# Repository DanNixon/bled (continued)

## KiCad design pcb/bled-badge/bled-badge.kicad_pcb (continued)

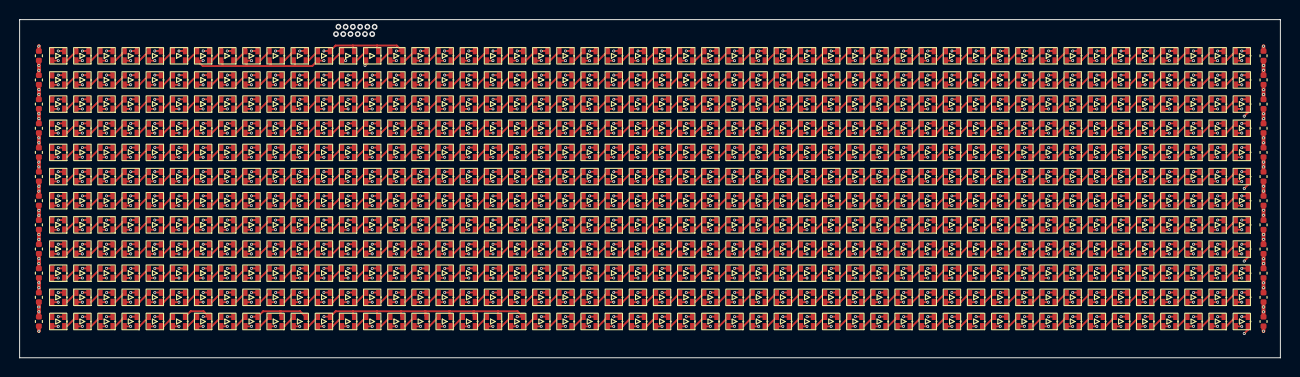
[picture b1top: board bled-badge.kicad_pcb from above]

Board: 4 copper layers, 130.5 x 35.0 mm, 625 parts (1 on the bottom side), 602 nets.

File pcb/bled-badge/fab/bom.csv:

Comment,Designator,Footprint,LCSC
10u,"C1,C2,C3,C4,C5,C6,C7,C8,C9,C10,C11,C12,C13,C14,C15,C16,C17,C18,C19,C20,C21,C22,C23,C24",Capacitor_SMD:C_0402_1005Metric,C15525
,U1,bled:BLED_Stamp,
XL-1615RGBC-WS2812B-S,"D1,D2,D3,D4,D5,D6,D7,D8,D9,D10,D11,D12,D13,D14,D15,D16,D17,D18,D19,D20,D21,D22,D23,D24,D25,D26,D27,D28,D29,D30,D31,D32,D33,D34,D35,D36,D37,D38,D39,D40,D41,D42,D43,D44,D45,D46,D47,D48,D49,D50,D51,D52,D53,D54,D55,D56,D57,D58,D59,D60,D61,D62,D63,D64,D65,D66,D67,D68,D69,D70,D71,D72,D73,D74,D75,D76,D77,D78,D79,D80,D81,D82,D83,D84,D85,D86,D87,D88,D89,D90,D91,D92,D93,D94,D95,D96,D97,D98,D99,D100",bled:XL-1615RGBC-2812B-S,C41413180
XL-1615RGBC-WS2812B-S,"D101,D102,D103,D104,D105,D106,D107,D108,D109,D110,D111,D112,D113,D114,D115,D116,D117,D118,D119,D120,D121,D122,D123,D124,D125,D126,D127,D128,D129,D130,D131,D132,D133,D134,D135,D136,D137,D138,D139,D140,D141,D142,D143,D144,D145,D146,D147,D148,D149,D150,D151,D152,D153,D154,D155,D156,D157,D158,D159,D160,D161,D162,D163,D164,D165,D166,D167,D168,D169,D170,D171,D172,D173,D174,D175,D176,D177,D178,D179,D180,D181,D182,D183,D184,D185,D186,D187,D188,D189,D190,D191,D192,D193,D194,D195,D196,D197,D198,D199,D200",bled:XL-1615RGBC-2812B-S,C41413180
XL-1615RGBC-WS2812B-S,"D201,D202,D203,D204,D205,D206,D207,D208,D209,D210,D211,D212,D213,D214,D215,D216,D217,D218,D219,D220,D221,D222,D223,D224,D225,D226,D227,D228,D229,D230,D231,D232,D233,D234,D235,D236,D237,D238,D239,D240,D241,D242,D243,D244,D245,D246,D247,D248,D249,D250,D251,D252,D253,D254,D255,D256,D257,D258,D259,D260,D261,D262,D263,D264,D265,D266,D267,D268,D269,D270,D271,D272,D273,D274,D275,D276,D277,D278,D279,D280,D281,D282,D283,D284,D285,D286,D287,D288,D289,D290,D291,D292,D293,D294,D295,D296,D297,D298,D299,D300",bled:XL-1615RGBC-2812B-S,C41413180
XL-1615RGBC-WS2812B-S,"D301,D302,D303,D304,D305,D306,D307,D308,D309,D310,D311,D312,D313,D314,D315,D316,D317,D318,D319,D320,D321,D322,D323,D324,D325,D326,D327,D328,D329,D330,D331,D332,D333,D334,D335,D336,D337,D338,D339,D340,D341,D342,D343,D344,D345,D346,D347,D348,D349,D350,D351,D352,D353,D354,D355,D356,D357,D358,D359,D360,D361,D362,D363,D364,D365,D366,D367,D368,D369,D370,D371,D372,D373,D374,D375,D376,D377,D378,D379,D380,D381,D382,D383,D384,D385,D386,D387,D388,D389,D390,D391,D392,D393,D394,D395,D396,D397,D398,D399,D400",bled:XL-1615RGBC-2812B-S,C41413180
XL-1615RGBC-WS2812B-S,"D401,D402,D403,D404,D405,D406,D407,D408,D409,D410,D411,D412,D413,D414,D415,D416,D417,D418,D419,D420,D421,D422,D423,D424,D425,D426,D427,D428,D429,D430,D431,D432,D433,D434,D435,D436,D437,D438,D439,D440,D441,D442,D443,D444,D445,D446,D447,D448,D449,D450,D451,D452,D453,D454,D455,D456,D457,D458,D459,D460,D461,D462,D463,D464,D465,D466,D467,D468,D469,D470,D471,D472,D473,D474,D475,D476,D477,D478,D479,D480,D481,D482,D483,D484,D485,D486,D487,D488,D489,D490,D491,D492,D493,D494,D495,D496,D497,D498,D499,D500",bled:XL-1615RGBC-2812B-S,C41413180
XL-1615RGBC-WS2812B-S,"D501,D502,D503,D504,D505,D506,D507,D508,D509,D510,D511,D512,D513,D514,D515,D516,D517,D518,D519,D520,D521,D522,D523,D524,D525,D526,D527,D528,D529,D530,D531,D532,D533,D534,D535,D536,D537,D538,D539,D540,D541,D542,D543,D544,D545,D546,D547,D548,D549,D550,D551,D552,D553,D554,D555,D556,D557,D558,D559,D560,D561,D562,D563,D564,D565,D566,D567,D568,D569,D570,D571,D572,D573,D574,D575,D576,D577,D578,D579,D580,D581,D582,D583,D584,D585,D586,D587,D588,D589,D590,D591,D592,D593,D594,D595,D596,D597,D598,D599,D600",bled:XL-1615RGBC-2812B-S,C41413180

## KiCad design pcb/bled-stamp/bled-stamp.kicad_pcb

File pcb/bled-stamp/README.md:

# BLED stamp

A small stamp-like PCB that can be designed onto lights, etc.
Mostly equivalent to the [backpack PCB](../bled-pico-w-backpack), but with a BMS and in a form factor easier to mount onto a larger PCB.

Features:

- All of the features of the backpack PCB
- Single cell lipo battery charging/management
- Some extra IO on the castellations
- USB C (with debug on sideband pins)

## Power

There are three main options for powering an installation with the stamp:

### 1) USB only

- Do not connect a lipo battery
- Do not connect a 5V supply to "5V IN"
- Power LEDs from "5V OUT"

### 2) battery

- Connect a single cell lipo battery to either the onboard connector or "BATT+", not both
- Do not connect a 5V supply to "5V IN"
- Power LEDs from "5V OUT"

When USB is also connected, LEDs will be powered from VBUS and battery will be recharged.

It is possible to turn off the LED power whilst leaving the MCU powered for low power standby.

### 3) external

- Do not connect a lipo battery
- Connect a 5V supply to "5V IN"
- Power LEDs from the external supply, not "5V OUT"

When USB is connected, logic will be powered from the higher of VBUS or "5V IN".

## Testing

Hardware testing checklist:

- Power from USB A-C cable in both orientations
- Power from USB C-C cable in both orientations
- Flashing firmware via SWD on type C sideband pins
- USB data
- User buttons
- SD card slot
- LED outputs
- Boot MCU into bootloader mode
- BMS
  - Interface with MCU
  - Power from battery
  - Battery charging
  - Boost converter working (5V LED power)
- BLE interface (if RM2 fitted)

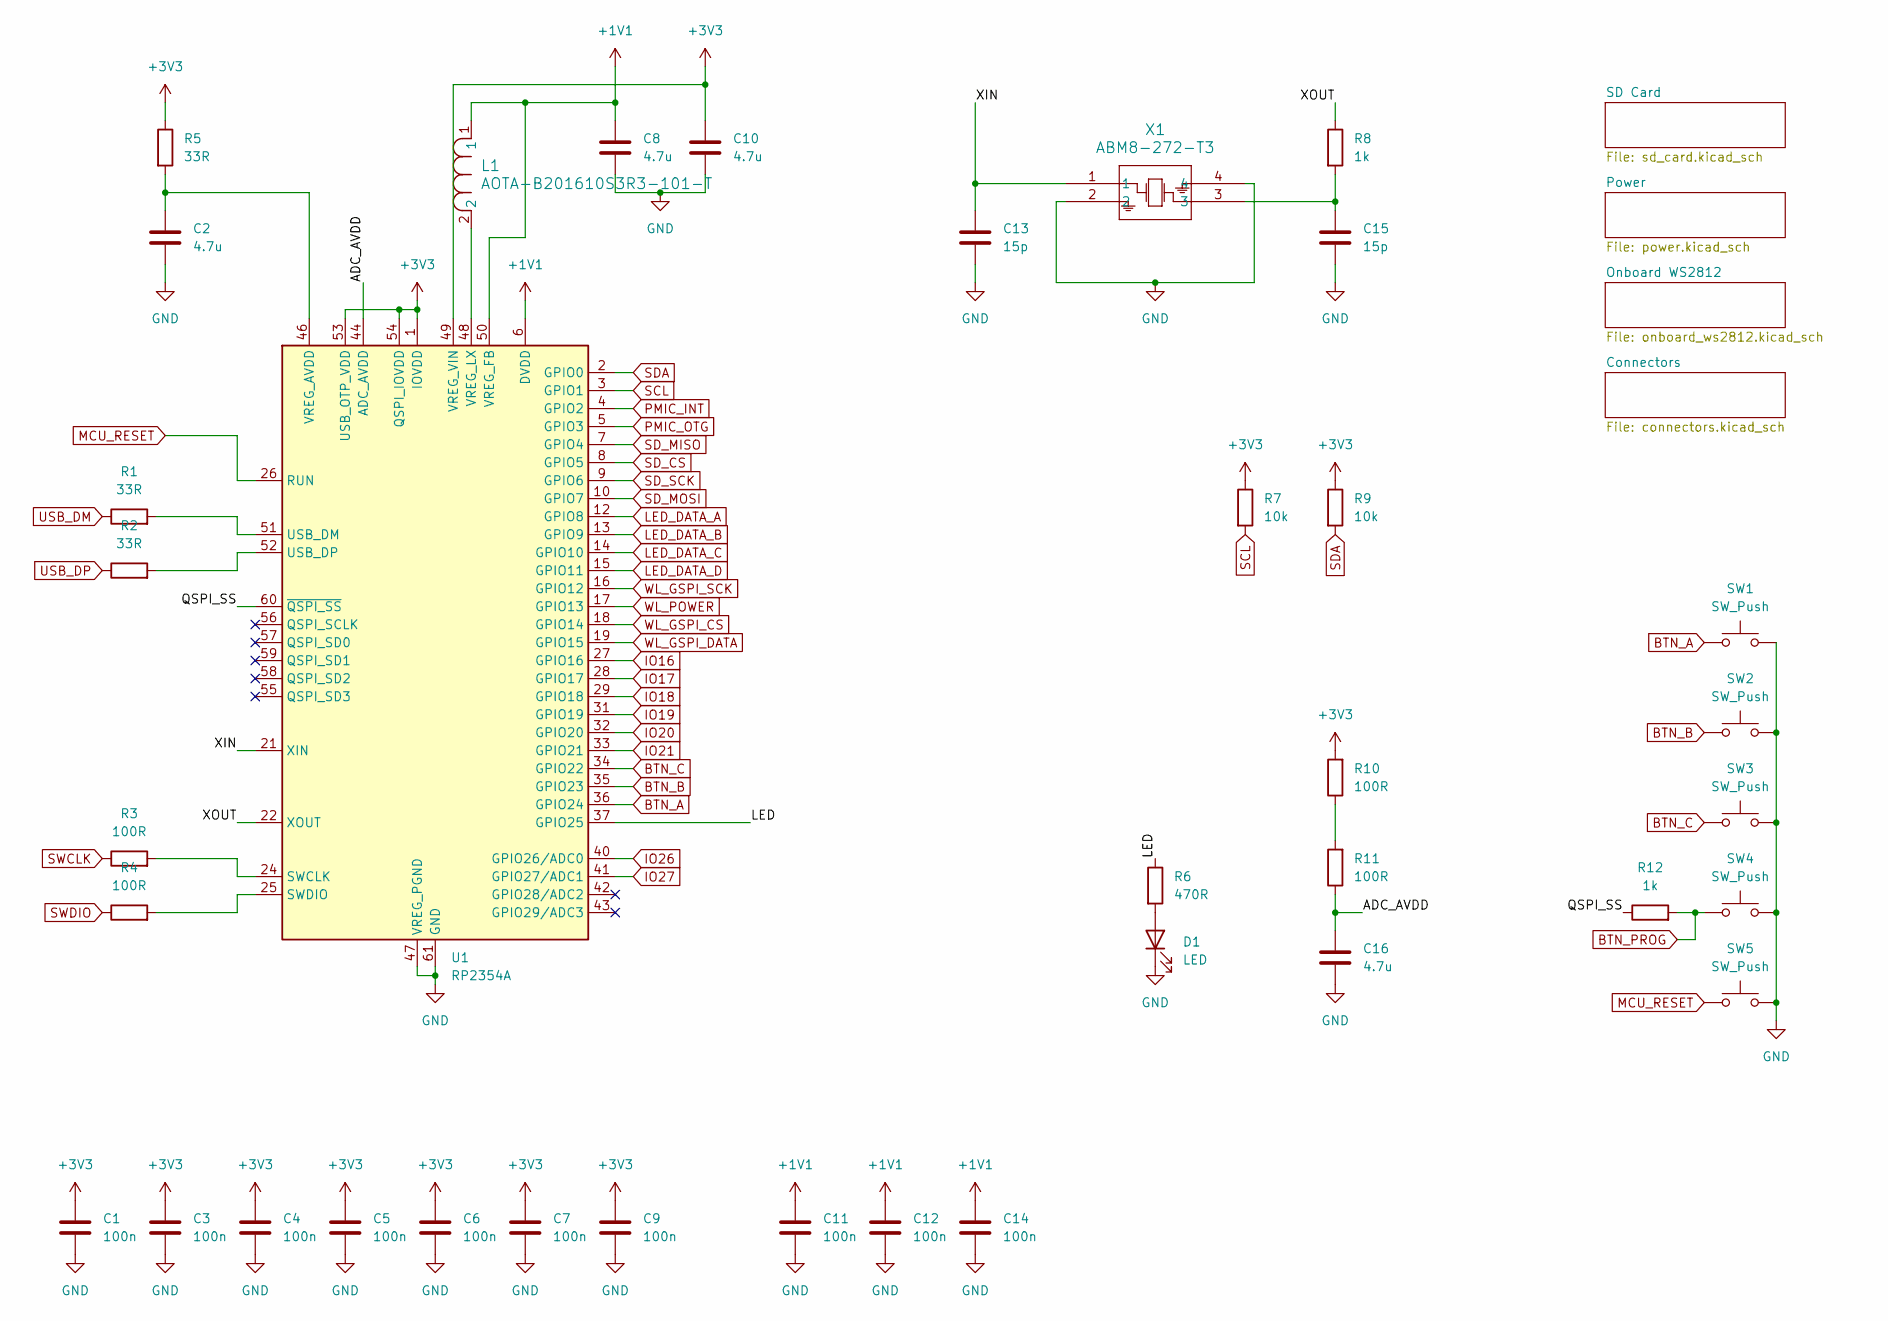
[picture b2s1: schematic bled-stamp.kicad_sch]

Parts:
C1, C3, C4, C5, C6, C7, C9, C11, C12, C14: 100n; C_0402_1005Metric; LCSC C1525
C2, C8, C10, C16: 4.7u; C_0402_1005Metric; LCSC C23733
C13, C15: 15p; C_0402_1005Metric; LCSC C1548
D1: LED; LED_0603_1608Metric; LCSC C2286
L1: AOTA-B201610S3R3-101-T; IND_AOTA-B201610S_2p0x1p6x1p0_ABR-L; LCSC C42411119
R1, R2, R5: 33R; R_0402_1005Metric; LCSC C25105
R3, R4, R10, R11: 100R; R_0402_1005Metric; LCSC C25076
R6: 470R; R_0402_1005Metric; LCSC C25117
R7, R9: 10k; R_0402_1005Metric; LCSC C25744
R8, R12: 1k; R_0402_1005Metric; LCSC C11702
SW1, SW2, SW3, SW4, SW5: SW_Push; SW_TS-1088_XNP; LCSC C720477
U1: RP2354A; QFN-60-1EP_7x7mm_P0.4mm_EP3.4x3.4mm; LCSC C41378174
X1: ABM8-272-T3; ABM8-272-T3_ABR; LCSC C20625731

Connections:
+1V1: C8.1, C11.1, C12.1, C14.1, L1.1, U1.6 (DVDD), U1.23 (DVDD), U1.39 (DVDD), U1.50 (VREG_FB)
+3V3: C1.1, C3.1, C4.1, C5.1, C6.1, C7.1, C9.1, C10.1, R5.1, R7.1, R9.1, R10.2, U1.1 (IOVDD), U1.11 (IOVDD), U1.20 (IOVDD), U1.30 (IOVDD), U1.38 (IOVDD), U1.45 (IOVDD), U1.49 (VREG_VIN), U1.53 (USB_OTP_VDD), U1.54 (QSPI_IOVDD); also elsewhere on the board
/ADC_AVDD: C16.1, R11.1, U1.44 (ADC_AVDD)
/LED: R6.1, U1.37 (GPIO25)
/QSPI_SS: R12.1, U1.60 (~QSPI_SS)
/XIN: C13.1, U1.21 (XIN), X1.1
/XOUT: R8.1, U1.22 (XOUT)
BTN_A: SW1.1, U1.36 (GPIO24); also elsewhere on the board
BTN_B: SW2.1, U1.35 (GPIO23); also elsewhere on the board
BTN_C: SW3.1, U1.34 (GPIO22); also elsewhere on the board
BTN_PROG: R12.2, SW4.1; also elsewhere on the board
GND: C1.2, C2.2, C3.2, C4.2, C5.2, C6.2, C7.2, C8.2, C9.2, C10.2, C11.2, C12.2, C13.2, C14.2, C15.2, C16.2, D1.1 (K), SW1.2, SW2.2, SW3.2, SW4.2, SW5.2, U1.47 (VREG_PGND), U1.61 (GND), X1.2, X1.4; also elsewhere on the board
IO16: U1.27 (GPIO16); also elsewhere on the board
IO17: U1.28 (GPIO17); also elsewhere on the board
IO18: U1.29 (GPIO18); also elsewhere on the board
IO19: U1.31 (GPIO19); also elsewhere on the board
IO20: U1.32 (GPIO20); also elsewhere on the board
IO21: U1.33 (GPIO21); also elsewhere on the board
IO26: U1.40 (GPIO26/ADC0); also elsewhere on the board
IO27: U1.41 (GPIO27/ADC1); also elsewhere on the board
LED_DATA_A: U1.12 (GPIO8); also elsewhere on the board
LED_DATA_B: U1.13 (GPIO9); also elsewhere on the board
LED_DATA_C: U1.14 (GPIO10); also elsewhere on the board
LED_DATA_D: U1.15 (GPIO11); also elsewhere on the board
MCU_RESET: SW5.1, U1.26 (RUN); also elsewhere on the board
unnamed: C15.1, R8.2, X1.3
unnamed: D1.2 (A), R6.2
unnamed: R10.1, R11.2
unnamed: R3.2, U1.24 (SWCLK)
unnamed: R4.2, U1.25 (SWDIO)
unnamed: R1.2, U1.51 (USB_DM)
unnamed: R2.2, U1.52 (USB_DP)
unnamed: C2.1, R5.2, U1.46 (VREG_AVDD)
unnamed: L1.2, U1.48 (VREG_LX)
PMIC_INT: U1.4 (GPIO2); also elsewhere on the board
PMIC_OTG: U1.5 (GPIO3); also elsewhere on the board
SCL: R7.2, U1.3 (GPIO1); also elsewhere on the board
SDA: R9.2, U1.2 (GPIO0); also elsewhere on the board
SD_CS: U1.8 (GPIO5); also elsewhere on the board
SD_MISO: U1.7 (GPIO4); also elsewhere on the board
SD_MOSI: U1.10 (GPIO7); also elsewhere on the board
SD_SCK: U1.9 (GPIO6); also elsewhere on the board
SWCLK: R3.1; also elsewhere on the board
SWDIO: R4.1; also elsewhere on the board
USB_DM: R1.1; also elsewhere on the board
USB_DP: R2.1; also elsewhere on the board
WL_GSPI_CS: U1.18 (GPIO14); also elsewhere on the board
WL_GSPI_DATA: U1.19 (GPIO15); also elsewhere on the board
WL_GSPI_SCK: U1.16 (GPIO12); also elsewhere on the board
WL_POWER: U1.17 (GPIO13); also elsewhere on the board

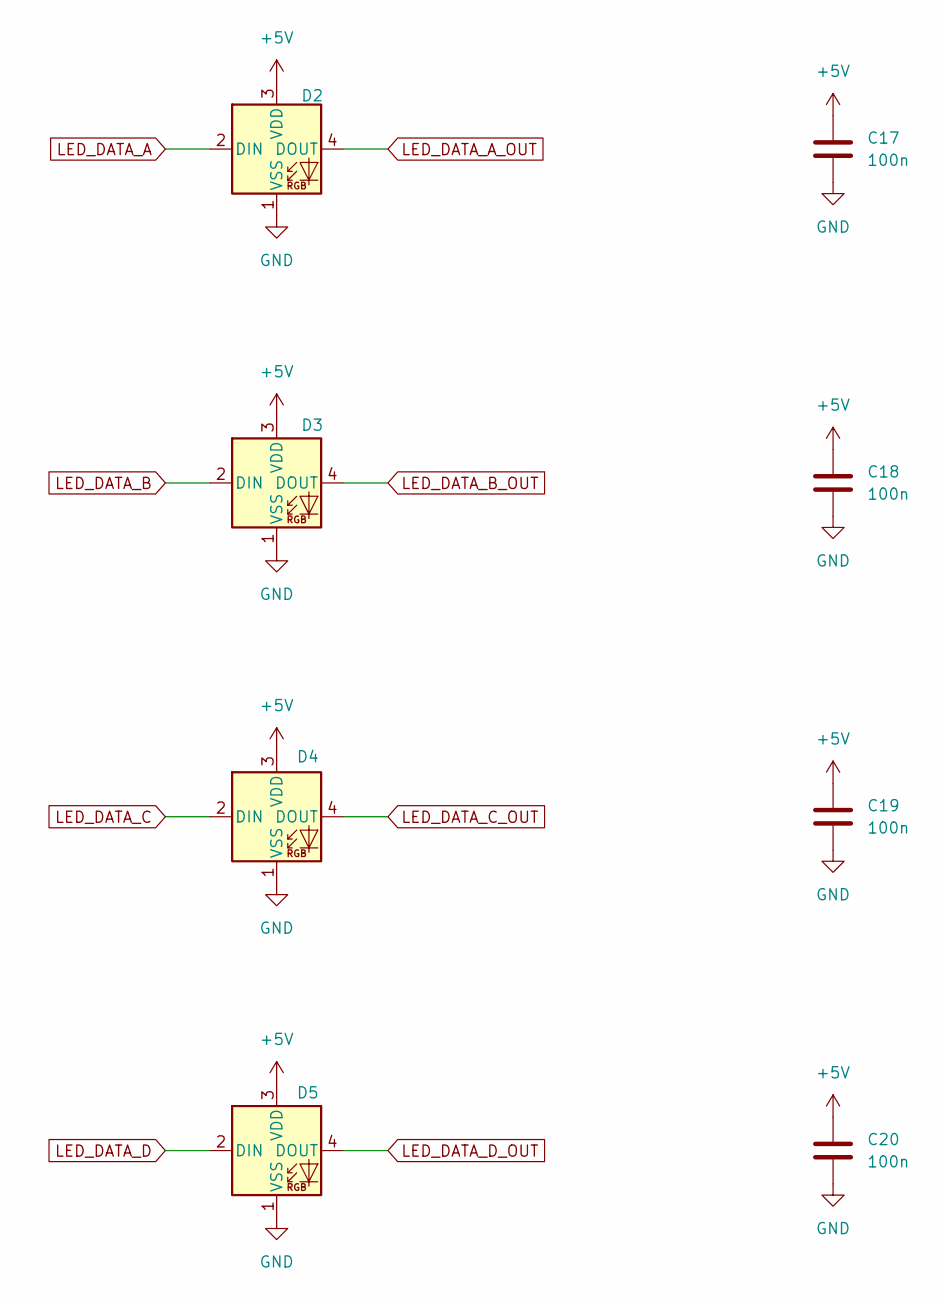
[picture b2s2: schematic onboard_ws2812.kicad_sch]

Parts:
C17, C18, C19, C20: 100n; C_0402_1005Metric; LCSC C1525
D2, D3, D4, D5: XL-1615RGBC-WS2812B; XL-1615RGBC-2812B; LCSC C5349954

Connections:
+5V: C17.1, C18.1, C19.1, C20.1, D2.3 (VDD), D3.3 (VDD), D4.3 (VDD), D5.3 (VDD); also elsewhere on the board
GND: C17.2, C18.2, C19.2, C20.2, D2.1 (VSS), D3.1 (VSS), D4.1 (VSS), D5.1 (VSS); also elsewhere on the board
LED_DATA_A: D2.2 (DIN); also elsewhere on the board
LED_DATA_A_OUT: D2.4 (DOUT); also elsewhere on the board
LED_DATA_B: D3.2 (DIN); also elsewhere on the board
LED_DATA_B_OUT: D3.4 (DOUT); also elsewhere on the board
LED_DATA_C: D4.2 (DIN); also elsewhere on the board
LED_DATA_C_OUT: D4.4 (DOUT); also elsewhere on the board
LED_DATA_D: D5.2 (DIN); also elsewhere on the board
LED_DATA_D_OUT: D5.4 (DOUT); also elsewhere on the board

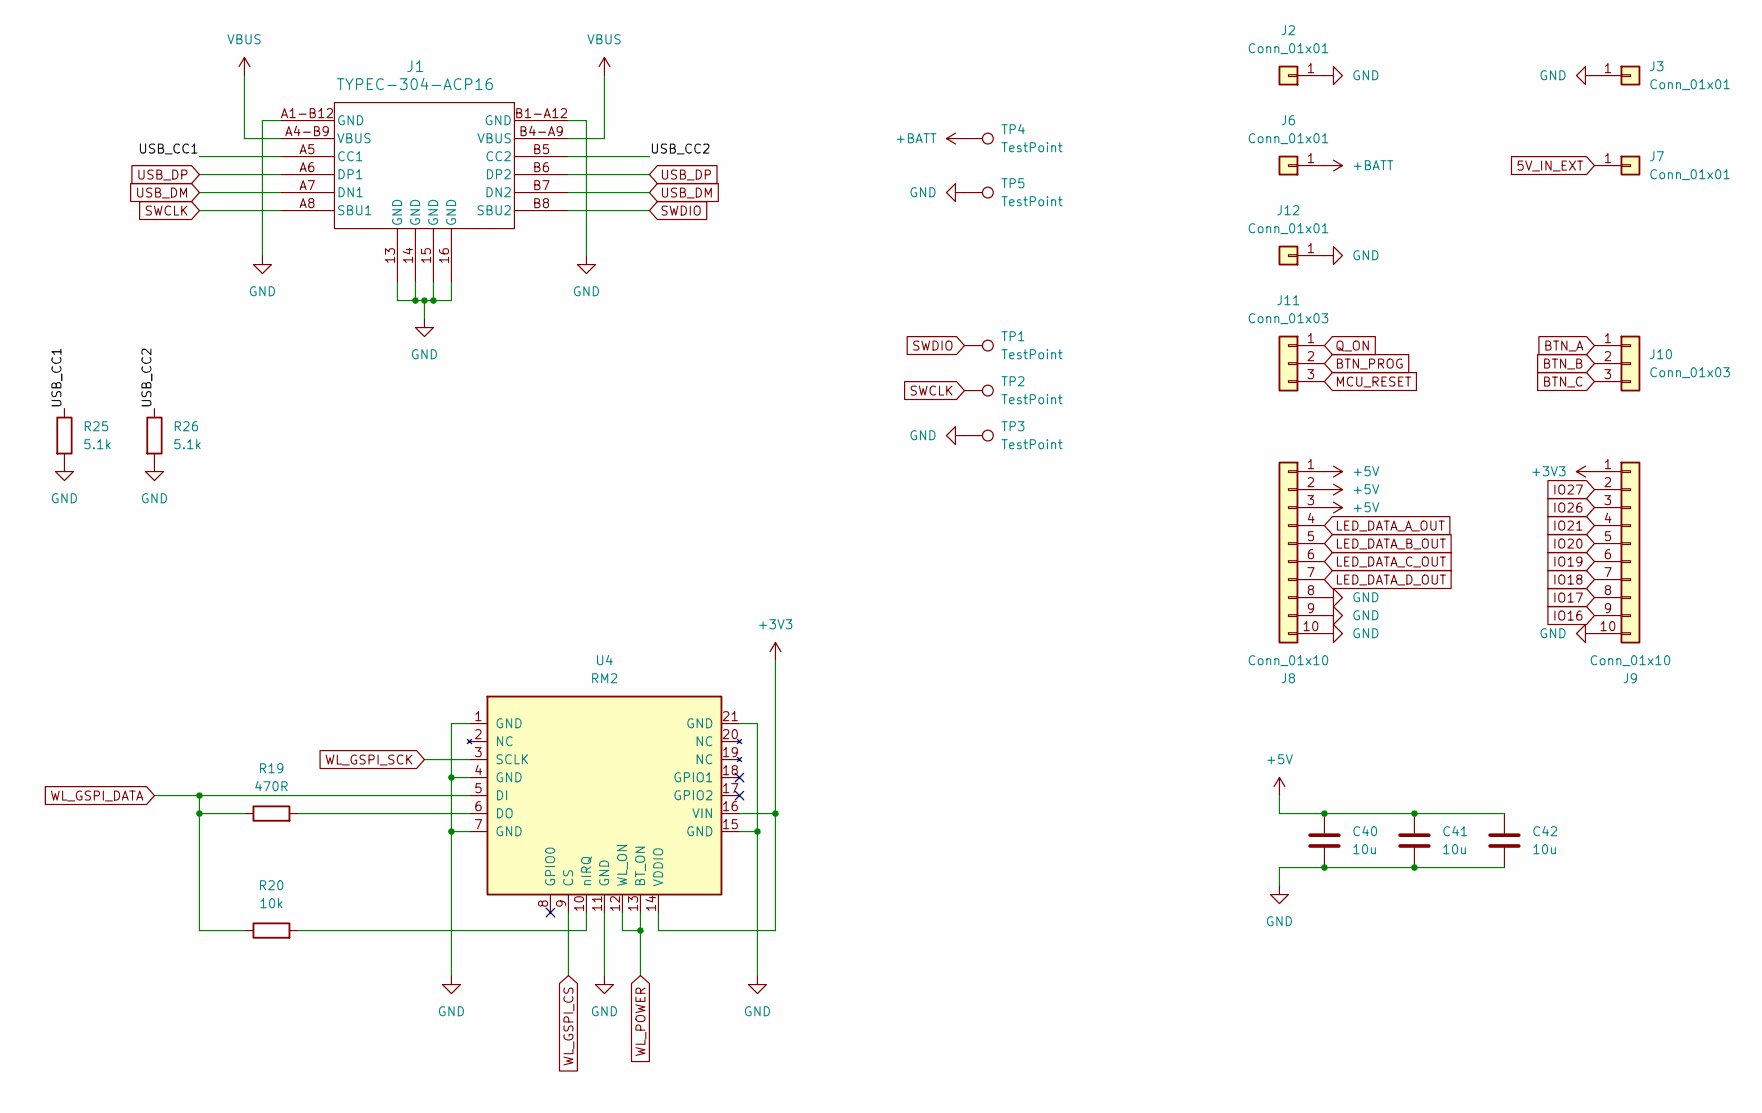
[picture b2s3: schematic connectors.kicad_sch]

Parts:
C40, C41, C42: 10u; C_0402_1005Metric; LCSC C15525
J1: TYPEC-304-ACP16; TYPEC-304-ACP16_XNP; LCSC C720630
J2, J3, J6, J7, J12: Conn_01x01; Castellation_Square_1pin
J8: Conn_01x10; Castellation_Stamp_Left
J9: Conn_01x10; Castellation_Stamp_Right
J10, J11: Conn_01x03; Castellation_Round_3pin
R19: 470R; R_0402_1005Metric; LCSC C25117
R20: 10k; R_0402_1005Metric; LCSC C25744
R25, R26: 5.1k; R_0402_1005Metric; LCSC C25905
TP1, TP2: TestPoint; TestPoint_Pad_D1.0mm
TP3: TestPoint; TestPoint_Pad_1.0x1.0mm
TP4, TP5: TestPoint; TestPoint_Pad_2.0x2.0mm
U4: RM2; RPI_RMC20452T

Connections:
5V_IN_EXT: J7.1 (Pin_1_1); also elsewhere on the board
+3V3: J9.1, U4.14 (VDDIO), U4.16 (VIN); also elsewhere on the board
+5V: C40.1, C41.1, C42.1, J8.1, J8.2, J8.3; also elsewhere on the board
+BATT: J6.1 (Pin_1_1), TP4.1 (1_1); also elsewhere on the board
/Connectors/USB_CC1: J1.A5 (CC1), R25.1
/Connectors/USB_CC2: J1.B5 (CC2), R26.1
BTN_A: J10.1; also elsewhere on the board
BTN_B: J10.2; also elsewhere on the board
BTN_C: J10.3; also elsewhere on the board
BTN_PROG: J11.2; also elsewhere on the board
GND: C40.2, C41.2, C42.2, J1.13 (GND), J1.14 (GND), J1.15 (GND), J1.16 (GND), J1.A1-B12 (GND), J1.B1-A12 (GND), J2.1 (Pin_1_1), J3.1 (Pin_1_1), J8.8, J8.9, J8.10, J9.10, J12.1 (Pin_1_1), R25.2, R26.2, TP3.1 (1_1), TP5.1 (1_1), U4.1 (GND), U4.4 (GND), U4.7 (GND), U4.11 (GND), U4.15 (GND), U4.21 (GND); also elsewhere on the board
IO16: J9.9; also elsewhere on the board
IO17: J9.8; also elsewhere on the board
IO18: J9.7; also elsewhere on the board
IO19: J9.6; also elsewhere on the board
IO20: J9.5; also elsewhere on the board
IO21: J9.4; also elsewhere on the board
IO26: J9.3; also elsewhere on the board
IO27: J9.2; also elsewhere on the board
LED_DATA_A_OUT: J8.4; also elsewhere on the board
LED_DATA_B_OUT: J8.5; also elsewhere on the board
LED_DATA_C_OUT: J8.6; also elsewhere on the board
LED_DATA_D_OUT: J8.7; also elsewhere on the board
MCU_RESET: J11.3; also elsewhere on the board
unnamed: R19.2, U4.6 (DO)
unnamed: R20.2, U4.10 (nIRQ)
Q_ON: J11.1; also elsewhere on the board
SWCLK: J1.A8 (SBU1), TP2.1 (1_1); also elsewhere on the board
SWDIO: J1.B8 (SBU2), TP1.1 (1_1); also elsewhere on the board
USB_DM: J1.A7 (DN1), J1.B7 (DN2); also elsewhere on the board
USB_DP: J1.A6 (DP1), J1.B6 (DP2); also elsewhere on the board
VBUS: J1.A4-B9 (VBUS), J1.B4-A9 (VBUS); also elsewhere on the board
WL_GSPI_CS: U4.9 (CS); also elsewhere on the board
WL_GSPI_DATA: R19.1, R20.1, U4.5 (DI); also elsewhere on the board
WL_GSPI_SCK: U4.3 (SCLK); also elsewhere on the board
WL_POWER: U4.12 (WL_ON), U4.13 (BT_ON); also elsewhere on the board

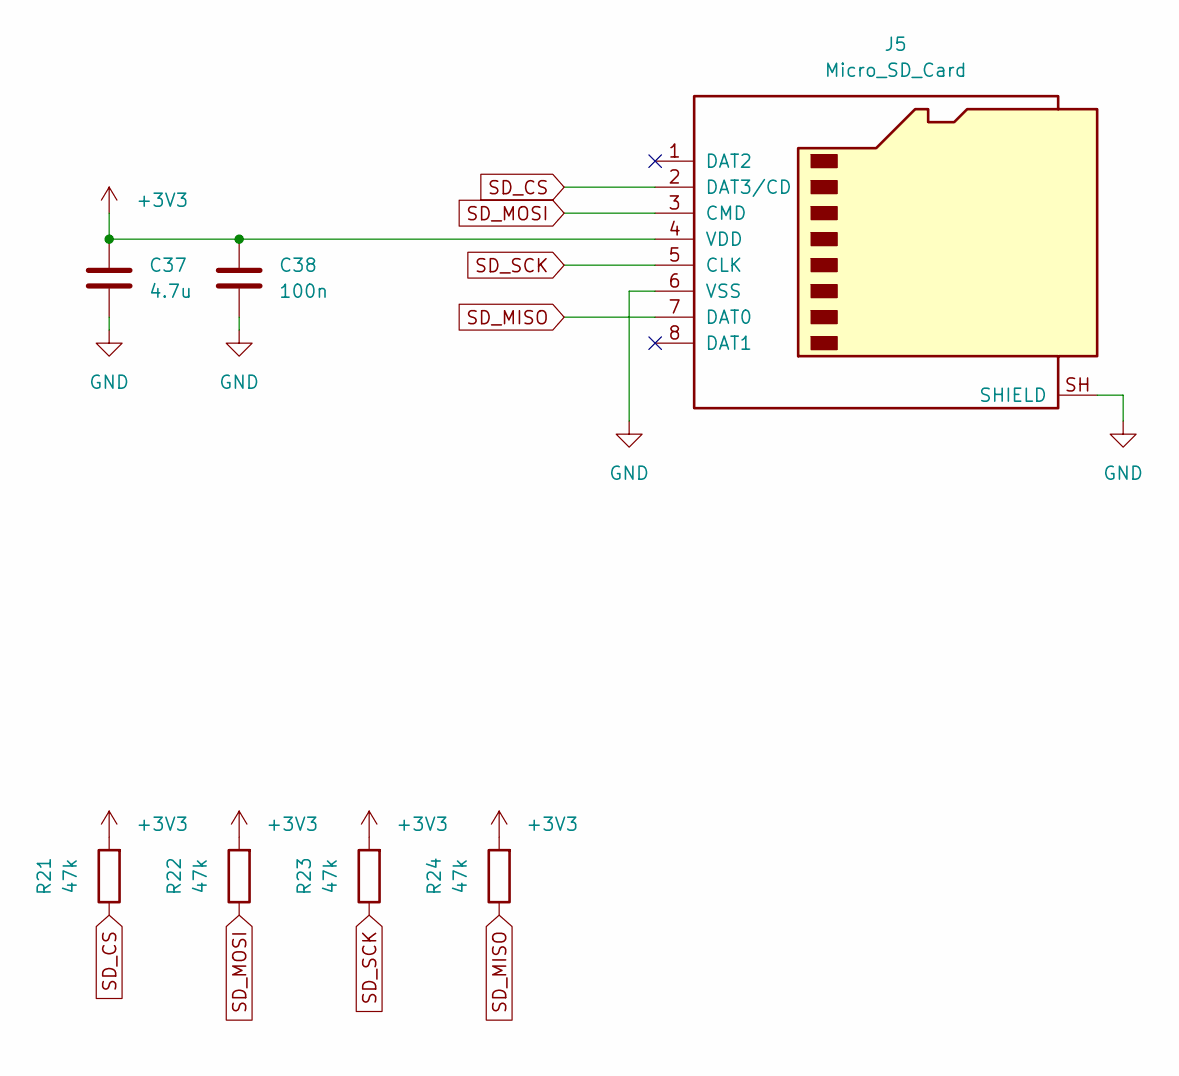
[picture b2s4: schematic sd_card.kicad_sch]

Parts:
C37: 4.7u; C_0402_1005Metric; LCSC C23733
C38: 100n; C_0402_1005Metric; LCSC C1525
J5: Micro_SD_Card; SD-Card-Deck-Hoauc-HYCW104-TF08-375B; LCSC C2962028
R21, R22, R23, R24: 47k; R_0402_1005Metric; LCSC C25792

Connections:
+3V3: C37.1, C38.1, J5.4 (VDD), R21.2, R22.2, R23.2, R24.2; also elsewhere on the board
GND: C37.2, C38.2, J5.6 (VSS), J5.SH (SHIELD); also elsewhere on the board
SD_CS: J5.2 (DAT3/CD), R21.1; also elsewhere on the board
SD_MISO: J5.7 (DAT0), R24.1; also elsewhere on the board
SD_MOSI: J5.3 (CMD), R22.1; also elsewhere on the board
SD_SCK: J5.5 (CLK), R23.1; also elsewhere on the board

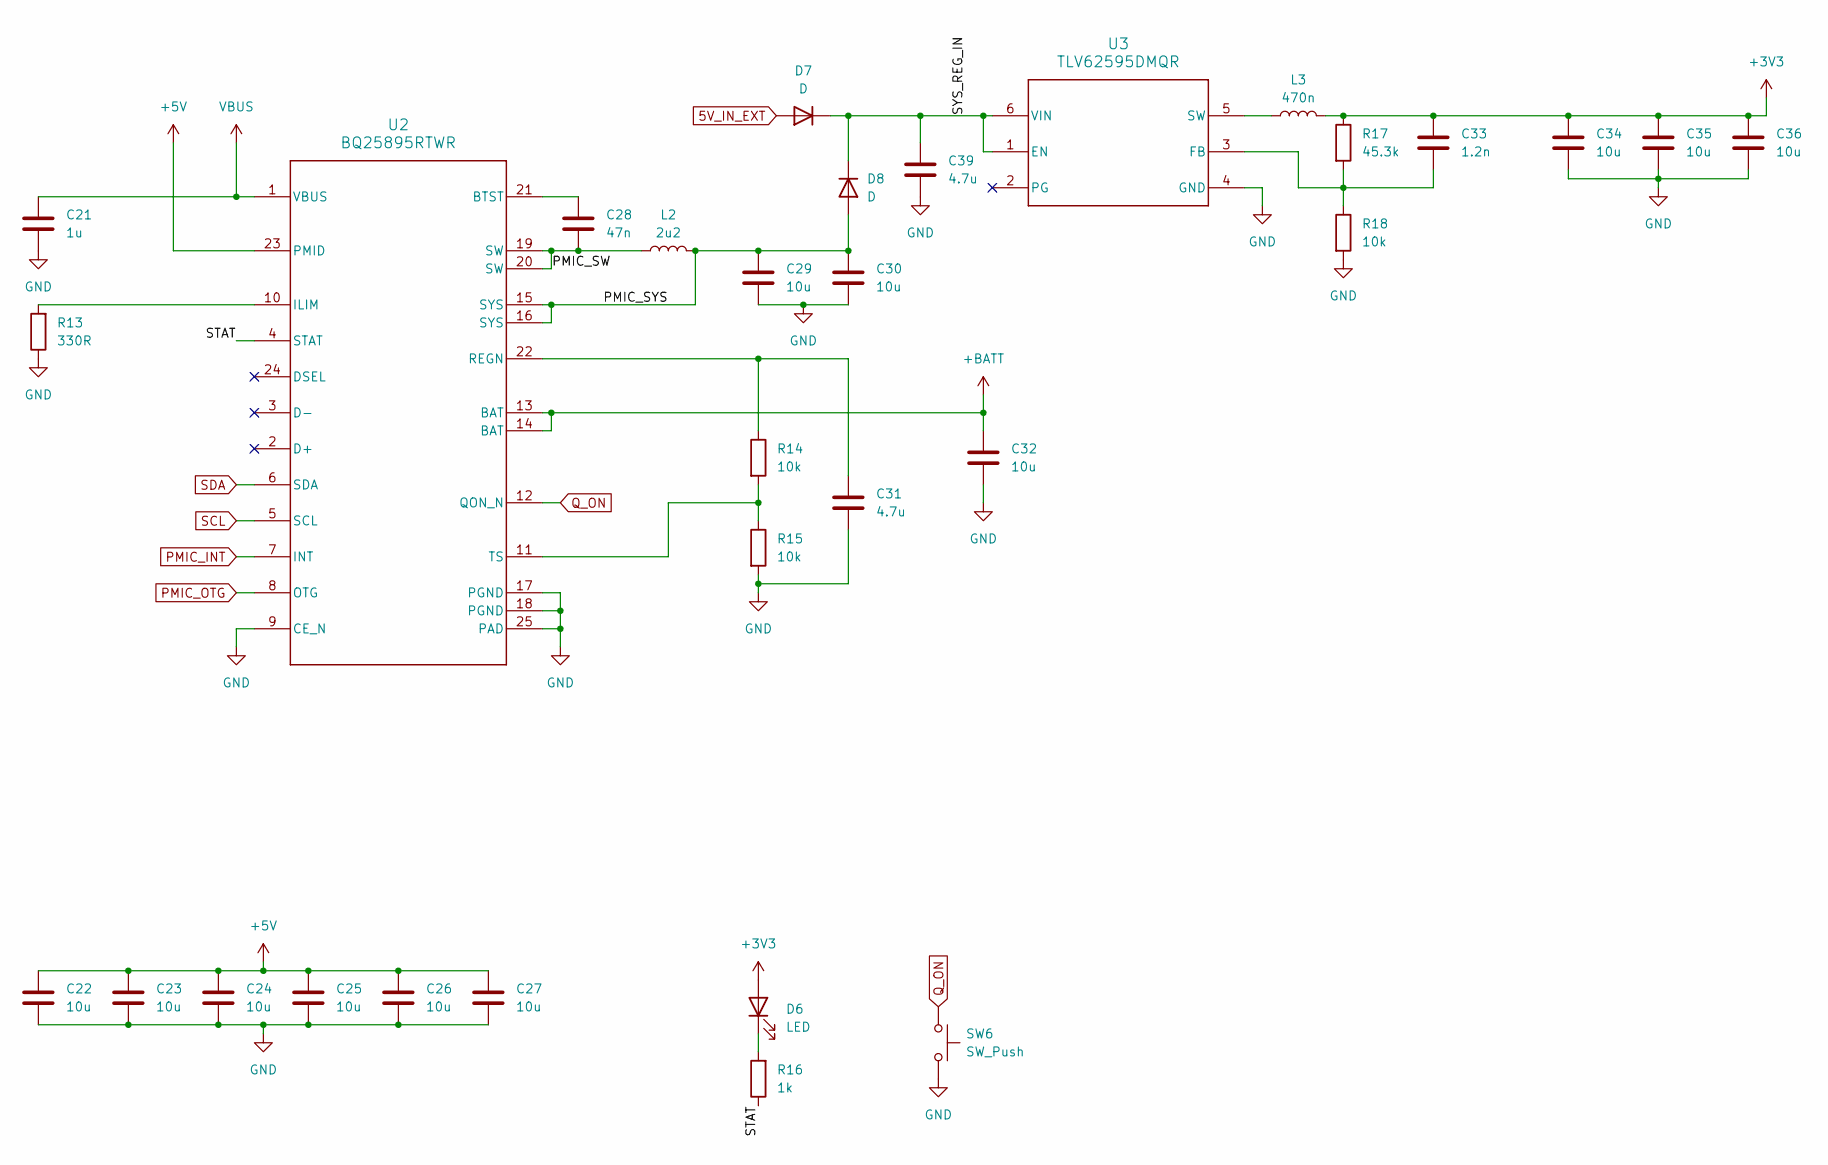
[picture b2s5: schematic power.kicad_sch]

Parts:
C21: 1u; C_0402_1005Metric; LCSC C52923
C22, C23, C24, C25, C26, C27, C29, C30, C32, C34, C35, C36: 10u; C_0402_1005Metric; LCSC C15525
C28: 47n; C_0402_1005Metric; LCSC C505498
C31, C39: 4.7u; C_0402_1005Metric; LCSC C23733
C33: 1.2n; C_0402_1005Metric; LCSC C107021
D6: LED; LED_0603_1608Metric; LCSC C2286
D7, D8: D; D_SOD-123; LCSC C50176370
L2: 2u2; YHNR4020; LCSC C2926400
L3: 470n; FTC252010S; LCSC C5832354
R13: 330R; R_0201_0603Metric; LCSC C473445
R14, R15, R18: 10k; R_0402_1005Metric; LCSC C25744
R16: 1k; R_0402_1005Metric; LCSC C11702
R17: 45.3k; R_0201_0603Metric; LCSC C473543
SW6: SW_Push; SW_TS-1088_XNP; LCSC C720477
U2: BQ25895RTWR; LCSC C80200
U3: TLV62595DMQR; DMQ0006A-MFG; LCSC C3189969

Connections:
5V_IN_EXT: D7.2 (A); also elsewhere on the board
+3V3: C33.1, C34.1, C35.1, C36.1, D6.2 (A), L3.2, R17.1; also elsewhere on the board
+5V: C22.1, C23.1, C24.1, C25.1, C26.1, C27.1, U2.23 (PMID); also elsewhere on the board
+BATT: C32.1, U2.13 (BAT), U2.14 (BAT); also elsewhere on the board
/Power/PMIC_SW: C28.2, L2.1, U2.19 (SW), U2.20 (SW)
/Power/PMIC_SYS: C29.1, C30.1, D8.2 (A), L2.2, U2.15 (SYS), U2.16 (SYS)
/Power/STAT: R16.1, U2.4 (STAT)
/Power/SYS_REG_IN: C39.1, D7.1 (K), D8.1 (K), U3.1 (EN), U3.6 (VIN)
GND: C21.2, C22.2, C23.2, C24.2, C25.2, C26.2, C27.2, C29.2, C30.2, C31.2, C32.2, C34.2, C35.2, C36.2, C39.2, R13.1, R15.2, R18.2, SW6.2, U2.9 (CE_N), U2.17 (PGND), U2.18 (PGND), U2.25 (PAD), U3.4 (GND); also elsewhere on the board
unnamed: D6.1 (K), R16.2
unnamed: C28.1, U2.21 (BTST)
unnamed: R13.2, U2.10 (ILIM)
unnamed: C31.1, R14.1, U2.22 (REGN)
unnamed: R14.2, R15.1, U2.11 (TS)
unnamed: C33.2, R17.2, R18.1, U3.3 (FB)
unnamed: L3.1, U3.5 (SW)
PMIC_INT: U2.7 (INT); also elsewhere on the board
PMIC_OTG: U2.8 (OTG); also elsewhere on the board
Q_ON: SW6.1, U2.12 (QON_N); also elsewhere on the board
SCL: U2.5 (SCL); also elsewhere on the board
SDA: U2.6 (SDA); also elsewhere on the board
VBUS: C21.1, U2.1 (VBUS); also elsewhere on the board

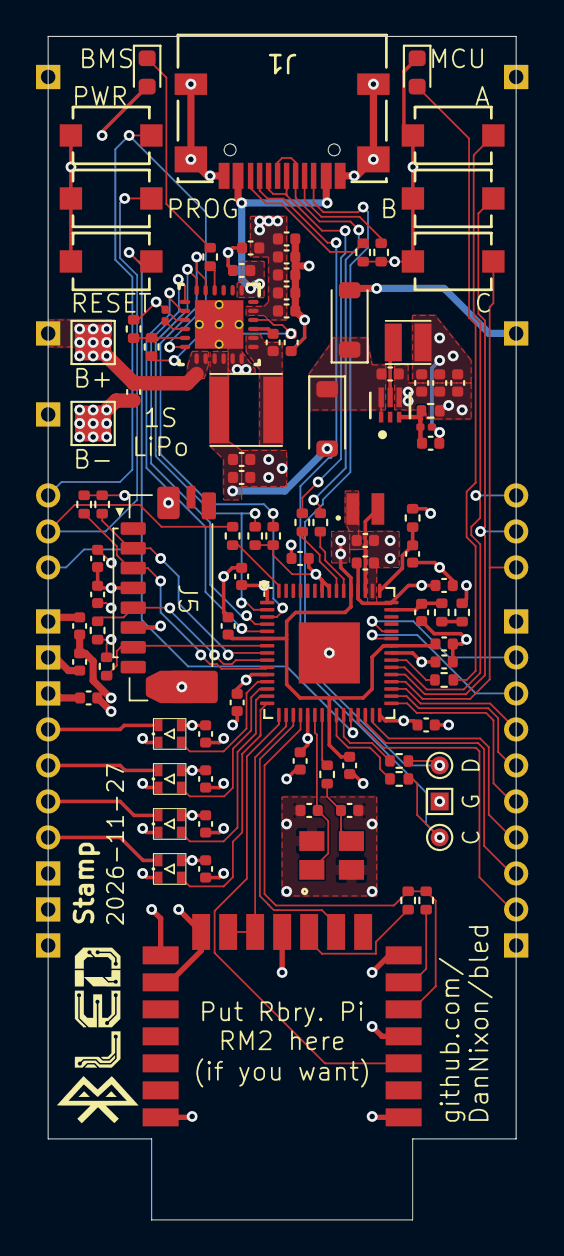
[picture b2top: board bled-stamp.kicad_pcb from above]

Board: 4 copper layers, 26.0 x 65.8 mm, 106 parts (0 on the bottom side), 74 nets.

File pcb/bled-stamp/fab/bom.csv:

Comment,Designator,Footprint,LCSC
SW_Push,"SW1,SW2,SW3,SW4,SW5,SW6",bled:SW_TS-1088_XNP,C720477
RP2354A,U1,Package_DFN_QFN:QFN-60-1EP_7x7mm_P0.4mm_EP3.4x3.4mm,C41378174
100n,"C1,C3,C4,C5,C6,C7,C9,C11,C12,C14,C17,C18,C19,C20,C38",Capacitor_SMD:C_0402_1005Metric,C1525
15p,"C13,C15",Capacitor_SMD:C_0402_1005Metric,C1548
100R,"R3,R4,R10,R11",Resistor_SMD:R_0201_0603Metric,C25076
33R,"R1,R2,R5",Resistor_SMD:R_0402_1005Metric,C25105
10k,"R7,R9,R14,R15,R18,R20",Resistor_SMD:R_0201_0603Metric,C25744
4.7u,"C2,C8,C10,C16,C31,C37,C39",Capacitor_SMD:C_0402_1005Metric,C23733
1k,"R8,R12,R16",Resistor_SMD:R_0402_1005Metric,C11702
ABM8-272-T3,X1,bled:ABM8-272-T3_ABR,C20625731
LED,"D1,D6",LED_SMD:LED_0603_1608Metric,C2286
470R,"R6,R19",Resistor_SMD:R_0201_0603Metric,C25117
AOTA-B201610S3R3-101-T,L1,bled:IND_AOTA-B201610S_2p0x1p6x1p0_ABR-L,C42411119
XL-1615RGBC-WS2812B,"D2,D3,D4,D5",bled:XL-1615RGBC-2812B,C5349954
Conn_01x01,"J2,J3,J6,J7",bled:Castellation_Square_1pin,
Conn_01x03,"J10,J11",bled:Castellation_Round_3pin,
TYPEC-304-ACP16,J1,bled:TYPEC-304-ACP16_XNP,C720630
TestPoint,"TP1,TP2",TestPoint:TestPoint_Pad_D1.0mm,
Conn_01x02,J4,bled:CONN_SM02B-SRSS-TB_JST,C160402
Conn_01x10,J8,bled:Castellation_Stamp_Left,
RM2,U4,bled:RPI_RMC20452T,
Conn_01x10,J9,bled:Castellation_Stamp_Right,
47k,"R21,R22,R23,R24",Resistor_SMD:R_0402_1005Metric,C25792
Micro_SD_Card,J5,bled:SD-Card-Deck-Hoauc-HYCW104-TF08-375B,C2962028
10u,"C22,C23,C24,C25,C26,C27,C29,C30,C32,C34,C35,C36",Capacitor_SMD:C_0402_1005Metric,C15525
BQ25895RTWR,U2,bled:BQ25895RTWR,C80200
47n,C28,Capacitor_SMD:C_0402_1005Metric,C505498
2u2,L2,bled:YHNR4020,C2926400
470n,L3,bled:FTC252010S,C5832354
D,"D7,D8",Diode_SMD:D_SOD-123,C50176370
330R,R13,Resistor_SMD:R_0201_0603Metric,C473445
1.2n,C33,Capacitor_SMD:C_0402_1005Metric,C107021
TLV62595DMQR,U3,bled:DMQ0006A-MFG,C3189969
1u,C21,Capacitor_SMD:C_0402_1005Metric,C52923
45.3k,R17,Resistor_SMD:R_0201_0603Metric,C473543
